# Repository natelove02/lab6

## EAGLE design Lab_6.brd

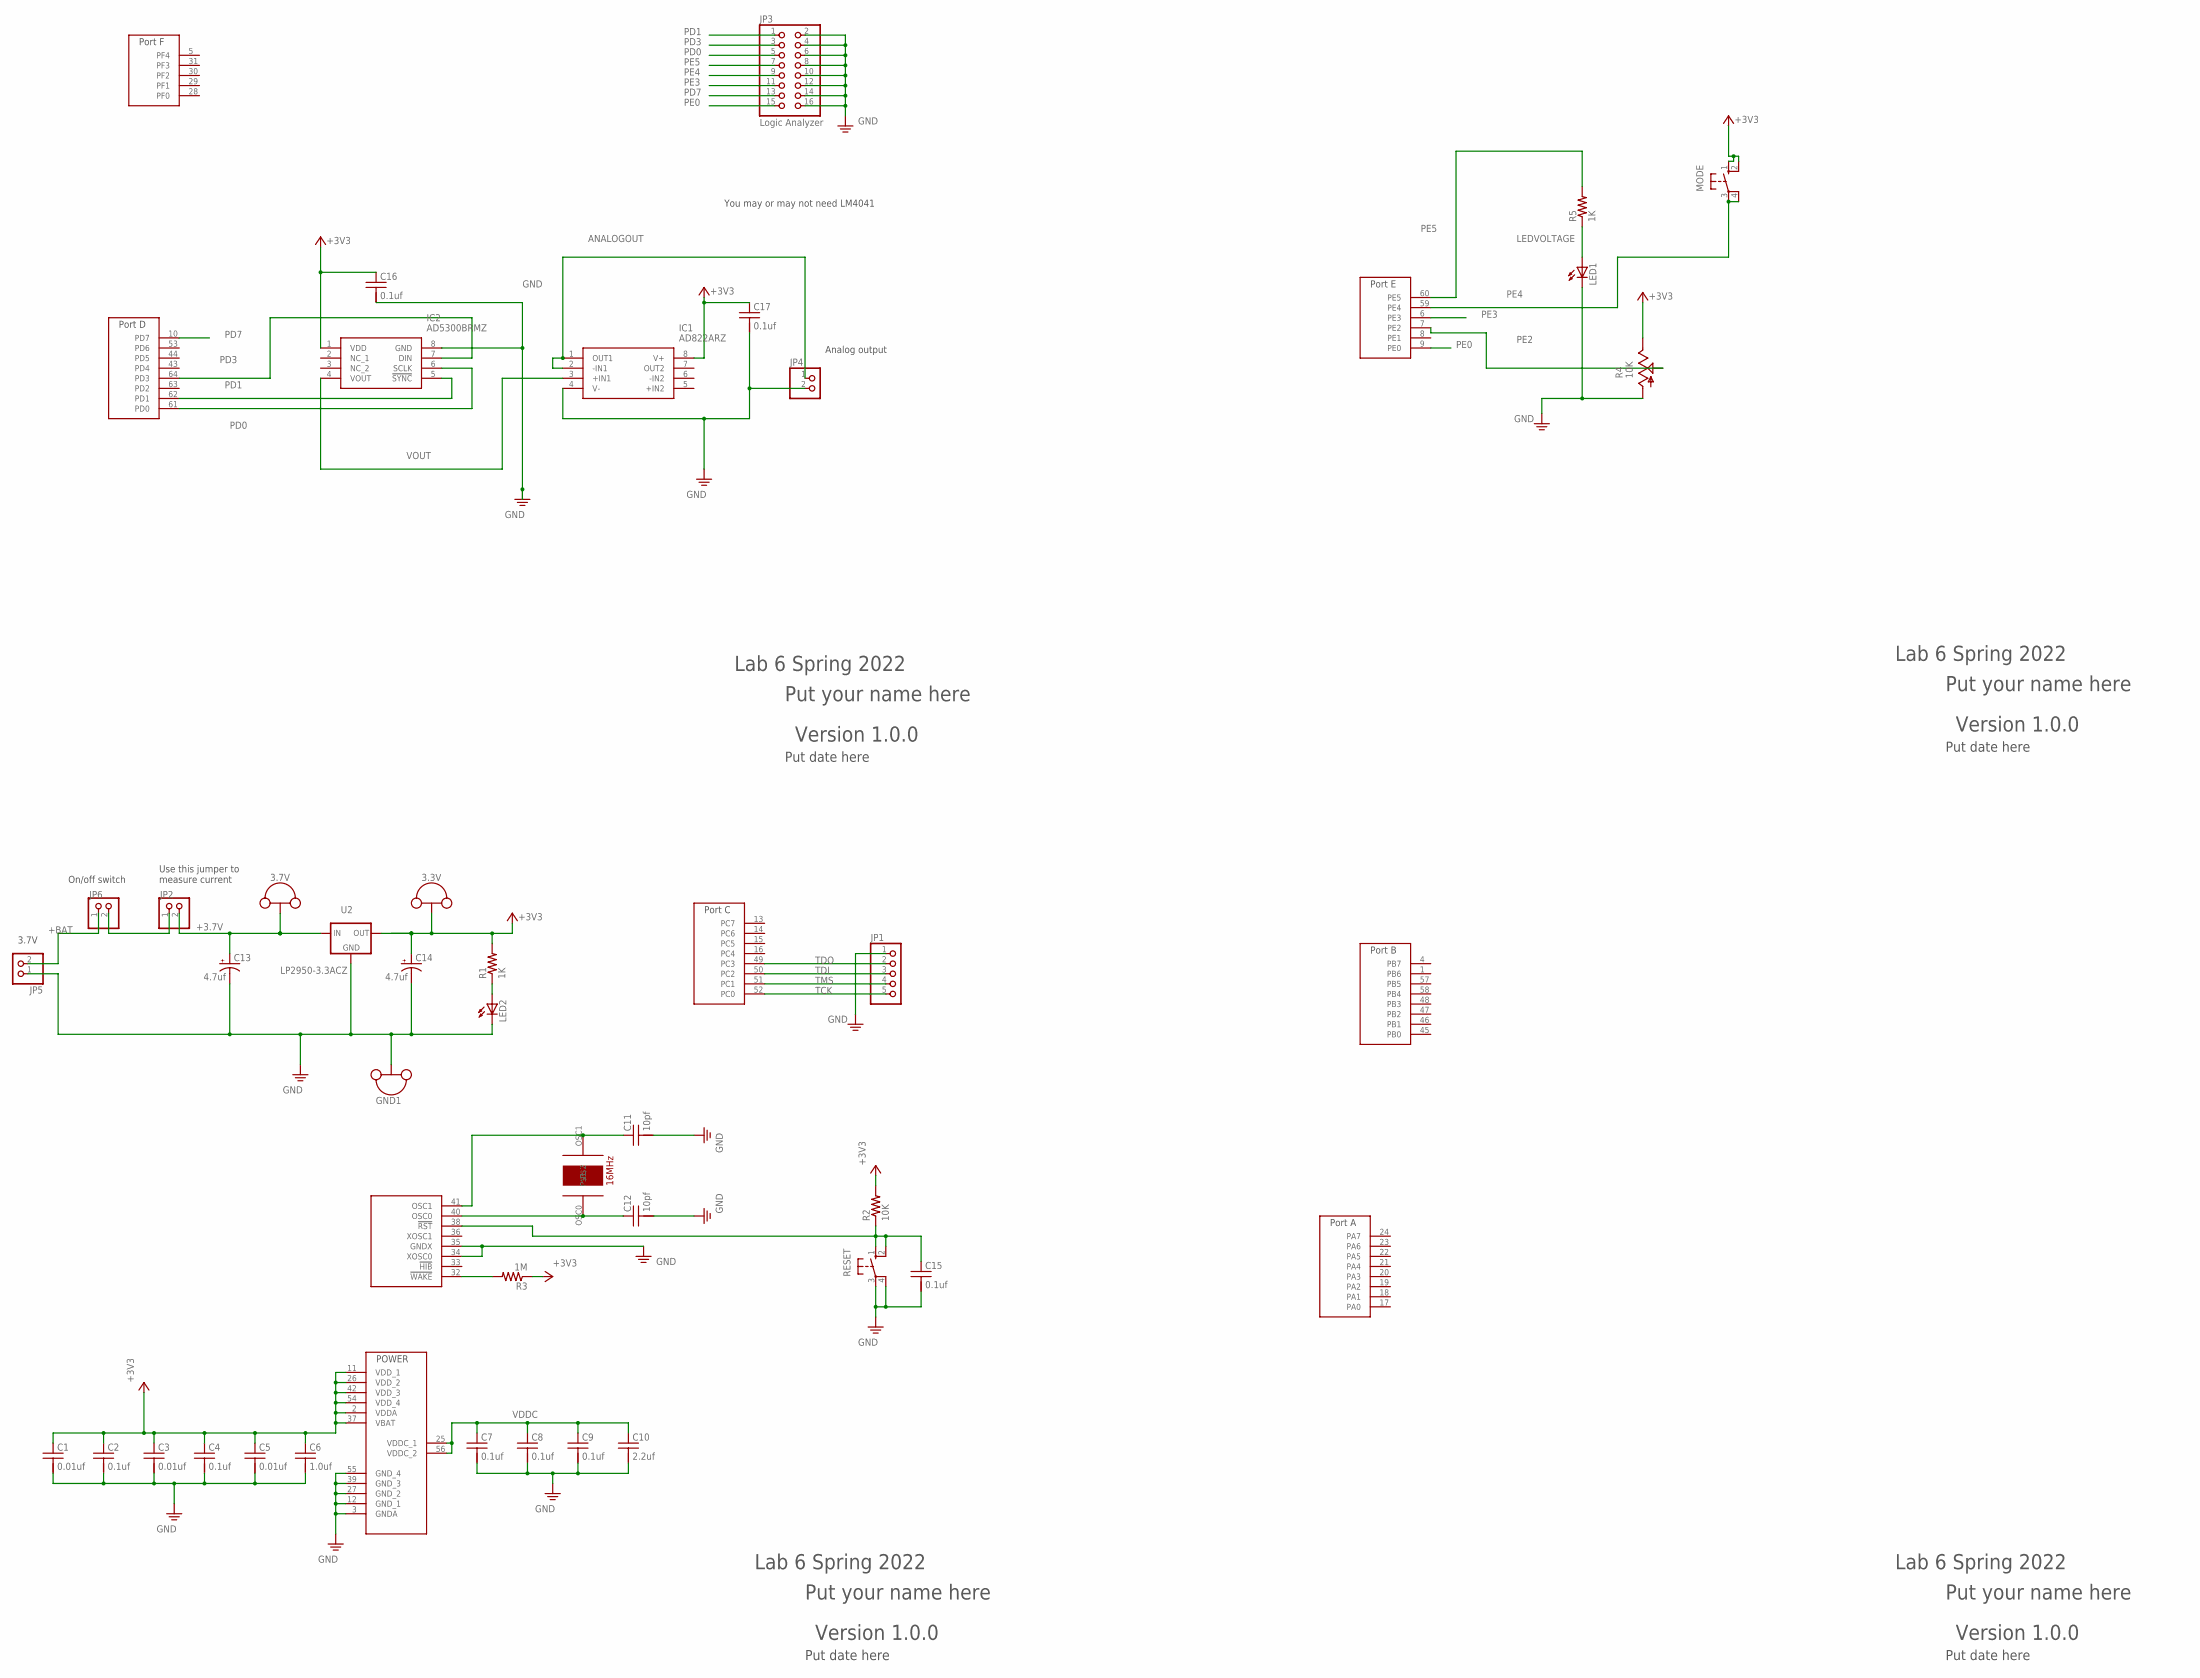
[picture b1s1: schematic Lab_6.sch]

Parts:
3.3V, 3.7V: TP_LOOP
C1, C3, C5: 0.01uf; CAP100MIL
C2, C4, C7, C8, C9, C15, C16, C17: 0.1uf; CAP100MIL
C6: 1.0uf; CAP100MIL
C10: 2.2uf; CAP100MIL
C11, C12: 10pf; CAP100MIL
C13, C14: 4.7uf; CAP200MILPOLARIZED
GND1: TP_LOOP
IC1: AD822ARZ; SOIC127P600X175-8N
IC2: AD5300BRMZ; SOP65P490X110-8N
JP1: PINHD-1X5; 1X05
JP2, JP4, JP5, JP6: PINHD-1X2; 1X02
JP3: Logic Analyzer; 2X08
LED1, LED2: LED3MM
MODE: B3F-1052; B3F-10XX
R1, R5: 1K; RES200MIL
R2: 10K; RES200MIL
R3: 1M; RES200MIL
R4: 10K; PTA2043
RESET: B3F-1052; B3F-10XX
U1: TM4C123GH6PM; QFP50P1200X1200X160-64N
U2: LP2950-3.3ACZ; TO92
Y1: 16MHZ_CRYSTAL

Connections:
+3.7V: 3.7V.P$1, 3.7V.P$2, C13.+, JP2.2, U2.3 (IN)
+3V3: 3.3V.P$1, 3.3V.P$2, C1.1, C2.1, C3.1, C4.1, C5.1, C6.1, C14.+, C16.1, C17.1, IC1.8 (V+), IC2.1 (VDD), MODE.1 (S), MODE.2 (S1), R1.2, R2.2, R3.1, R4.1 (E), U1.2 (VDDA), U1.11 (VDD_1), U1.26 (VDD_2), U1.37 (VBAT), U1.42 (VDD_3), U1.54 (VDD_4), U2.1 (OUT)
+BAT: JP5.2, JP6.1
ANALOGOUT: IC1.1 (OUT1), IC1.2 (-IN1), JP4.1
GND: C1.2, C2.2, C3.2, C4.2, C5.2, C6.2, C7.2, C8.2, C9.2, C10.2, C11.2, C12.2, C13.-, C14.-, C15.2, C16.2, C17.2, GND1.P$1, GND1.P$2, IC1.4 (V-), IC2.8 (GND), JP1.1, JP3.2, JP3.4, JP3.6, JP3.8, JP3.10, JP3.12, JP3.14, JP3.16, JP4.2, JP5.1, LED1.K (C), LED2.K (C), R4.3 (A), RESET.3, RESET.4 (P1), U1.3 (GNDA), U1.12 (GND_1), U1.27 (GND_2), U1.34 (XOSC0), U1.35 (GNDX), U1.39 (GND_3), U1.55 (GND_4), U2.2 (GND)
LEDVOLTAGE: LED1.A, R5.1
OSC0: C12.1, U1.40 (OSC0), Y1.OSC0
OSC1: C11.1, U1.41 (OSC1), Y1.OSC1
PD0: IC2.6 (SCLK), JP3.5, U1.61 (PD0)
PD1: IC2.5 (!SYNC), JP3.1, U1.62 (PD1)
PD3: IC2.7 (DIN), JP3.3, U1.64 (PD3)
PD7: JP3.13, U1.10 (PD7)
PE0: JP3.15, U1.9 (PE0)
PE2: R4.2 (S), U1.7 (PE2)
PE3: JP3.11, U1.6 (PE3)
PE4: JP3.9, MODE.3, MODE.4 (P1), U1.59 (PE4)
PE5: JP3.7, R5.2, U1.60 (PE5)
POWERLED: LED2.A, R1.1
RESET: C15.1, R2.1, RESET.1 (S), RESET.2 (S1), U1.38 (!RST)
SWITCHEDPOWER: JP2.1, JP6.2
TCK: JP1.5, U1.52 (PC0)
TDI: JP1.3, U1.50 (PC2)
TDO: JP1.2, U1.49 (PC3)
TMS: JP1.4, U1.51 (PC1)
VDDC: C7.1, C8.1, C9.1, C10.1, U1.25 (VDDC_1), U1.56 (VDDC_2)
VOUT: IC1.3 (+IN1), IC2.4 (VOUT)
WAKE: R3.2, U1.32 (!WAKE)

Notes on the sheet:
Use this jumper to measure current
Lab 6 Spring 2022
Put your name here
Version 1.0.0
Put date here
You may or may not need LM4041
3.7V
Analog output
On/off switch

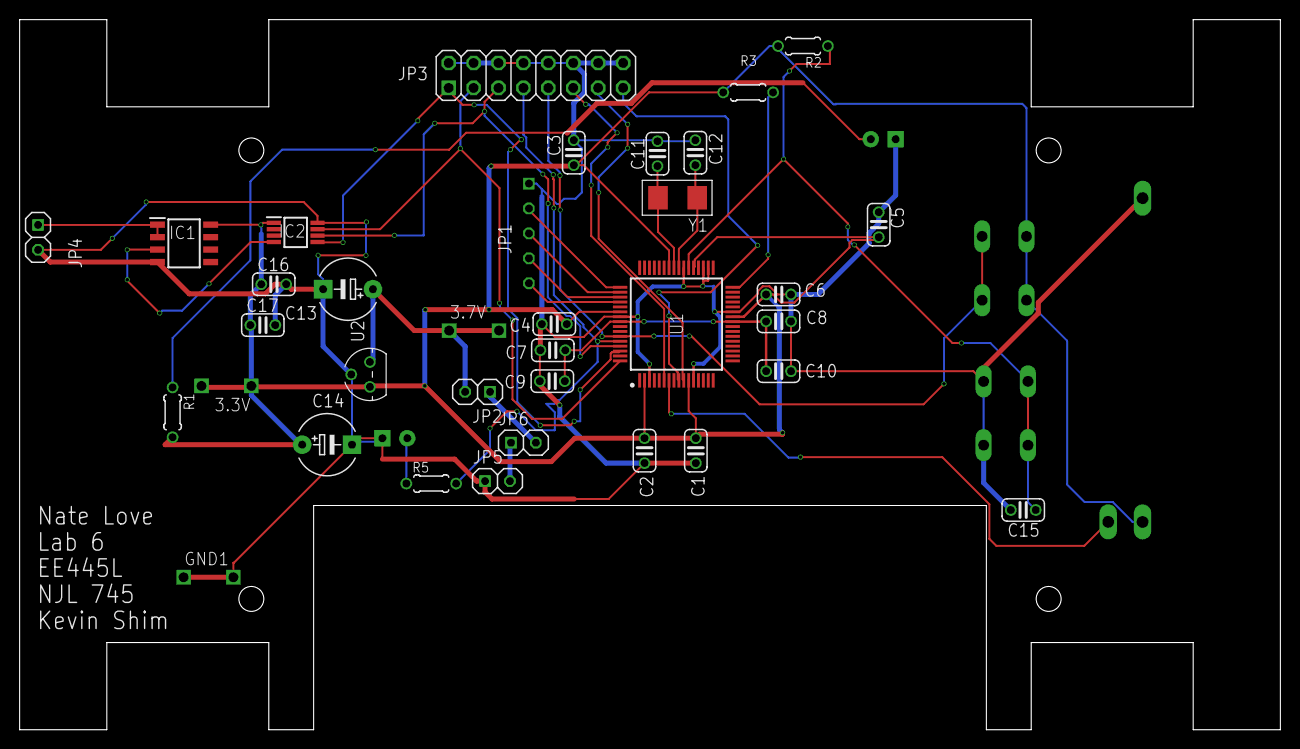
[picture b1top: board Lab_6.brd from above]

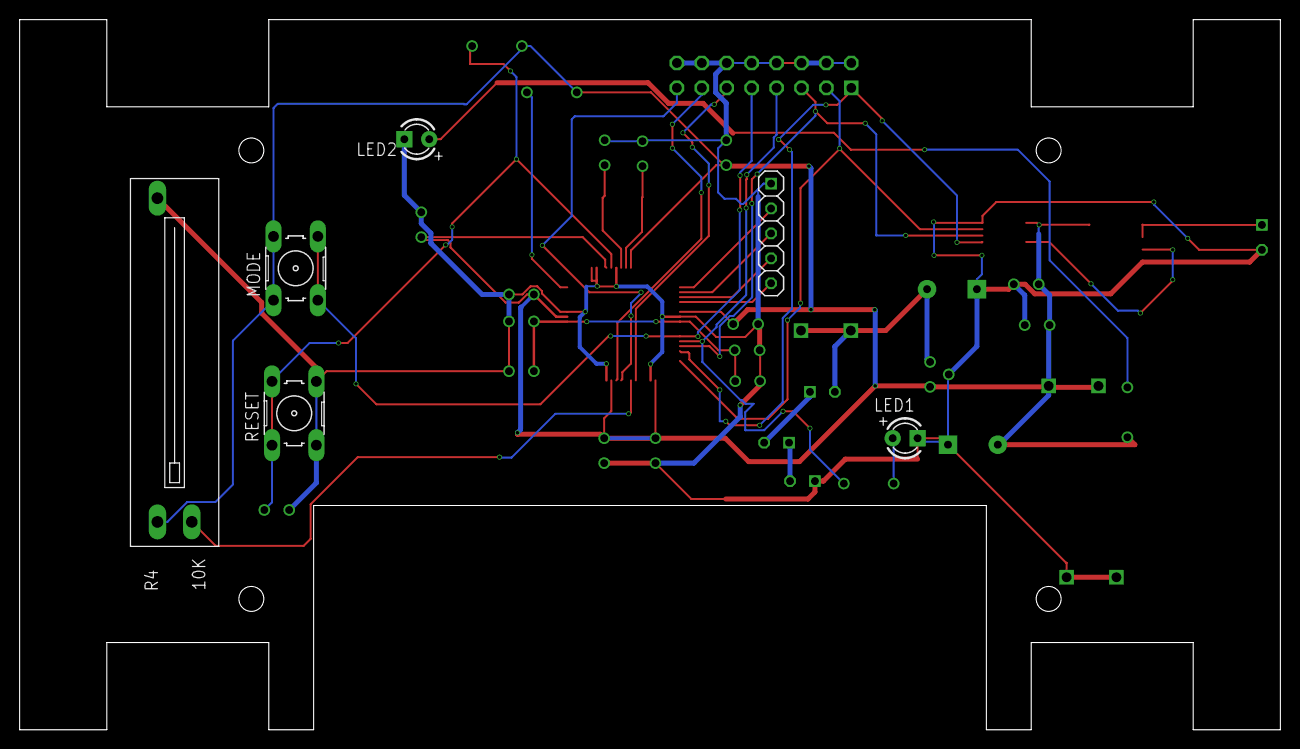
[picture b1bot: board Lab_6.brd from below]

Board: 2 copper layers, 128.5 x 72.4 mm, 40 parts (6 on the bottom side), 27 nets.
